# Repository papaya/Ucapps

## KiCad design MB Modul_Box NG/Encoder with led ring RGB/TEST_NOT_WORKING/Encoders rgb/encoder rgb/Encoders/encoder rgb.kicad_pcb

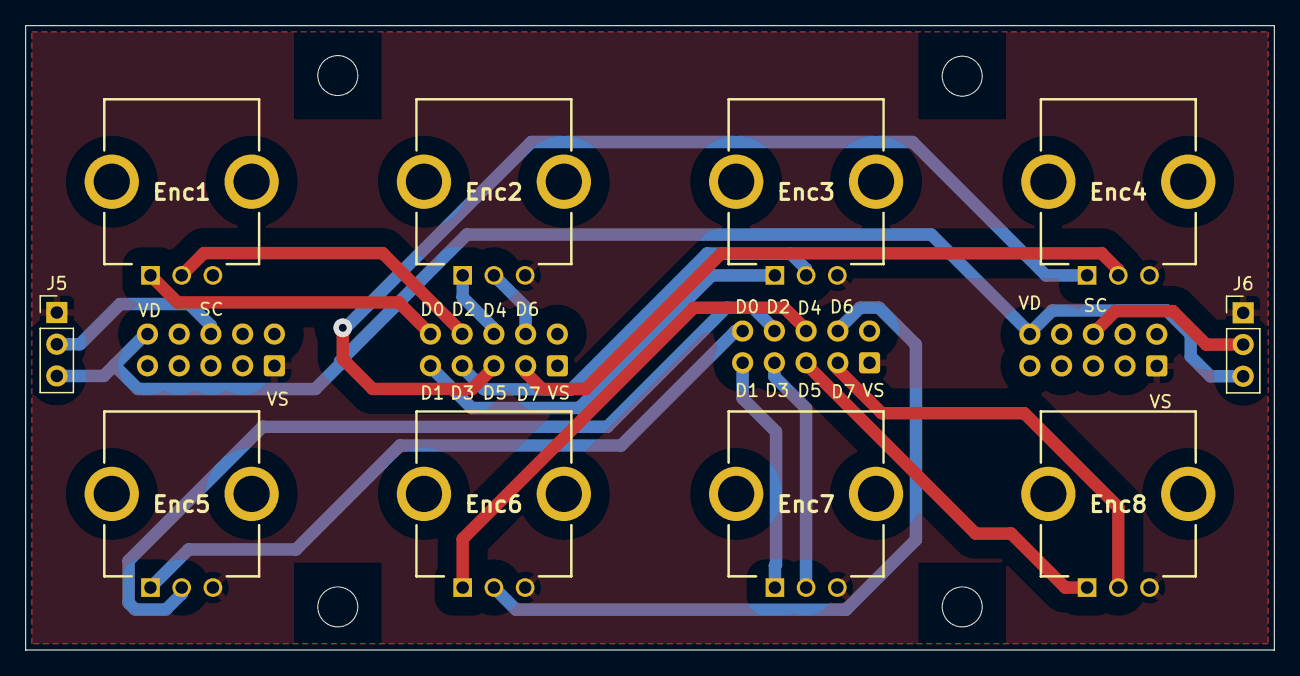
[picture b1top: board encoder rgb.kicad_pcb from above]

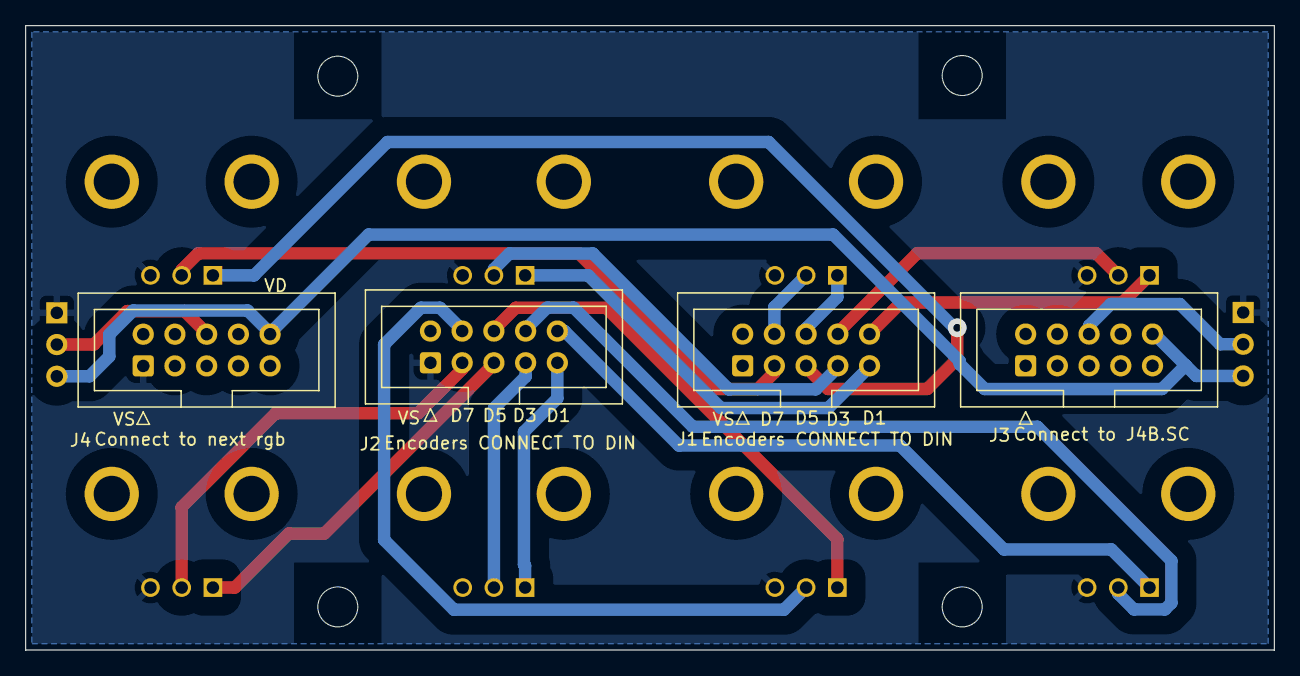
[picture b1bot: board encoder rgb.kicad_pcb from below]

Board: 2 copper layers, 100.0 x 50.0 mm, 18 parts (4 on the bottom side), 20 nets.

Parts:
Enc1, Enc2, Enc3, Enc4, Enc5, Enc6, Enc7, Enc8: RotaryEncoder; EC12E24204A8
H1, H2, H3, H4: MountingHole; MountingHole_3.2mm_M3
J1, J2, J3, J4: IDC-Header_2x05_P2.54mm_Vertical
J5, J6: Conn_01x03; PinHeader_1x03_P2.54mm_Vertical

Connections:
+5V: J3.10 (VD), J4.10 (VD), J5.3, J6.3
GND: Enc1.C, Enc2.C, Enc3.C, Enc4.C, Enc5.C, Enc6.C, Enc7.C, Enc8.C, J1.1 (vss), J2.1 (vss), J3.1 (vss), J4.1 (vss), J5.1, J6.1
unnamed: Enc1.A, J1.10 (D0)
unnamed: Enc3.A, J1.9 (D1)
unnamed: Enc1.B, J1.8 (D2)
unnamed: Enc3.B, J1.7 (D3)
unnamed: Enc2.A, J1.6 (D4)
unnamed: Enc4.A, J1.5 (D5)
unnamed: Enc2.B, J1.4 (D6)
unnamed: Enc4.B, J1.3 (D7)
unnamed: Enc5.A, J2.10 (D0)
unnamed: Enc7.A, J2.9 (D1)
unnamed: Enc5.B, J2.8 (D2)
unnamed: Enc7.B, J2.7 (D3)
unnamed: Enc6.A, J2.6 (D4)
unnamed: Enc8.A, J2.5 (D5)
unnamed: Enc6.B, J2.4 (D6)
unnamed: Enc8.B, J2.3 (D7)
unnamed: J3.6 (SC), J5.2
unnamed: J4.6 (SC), J6.2

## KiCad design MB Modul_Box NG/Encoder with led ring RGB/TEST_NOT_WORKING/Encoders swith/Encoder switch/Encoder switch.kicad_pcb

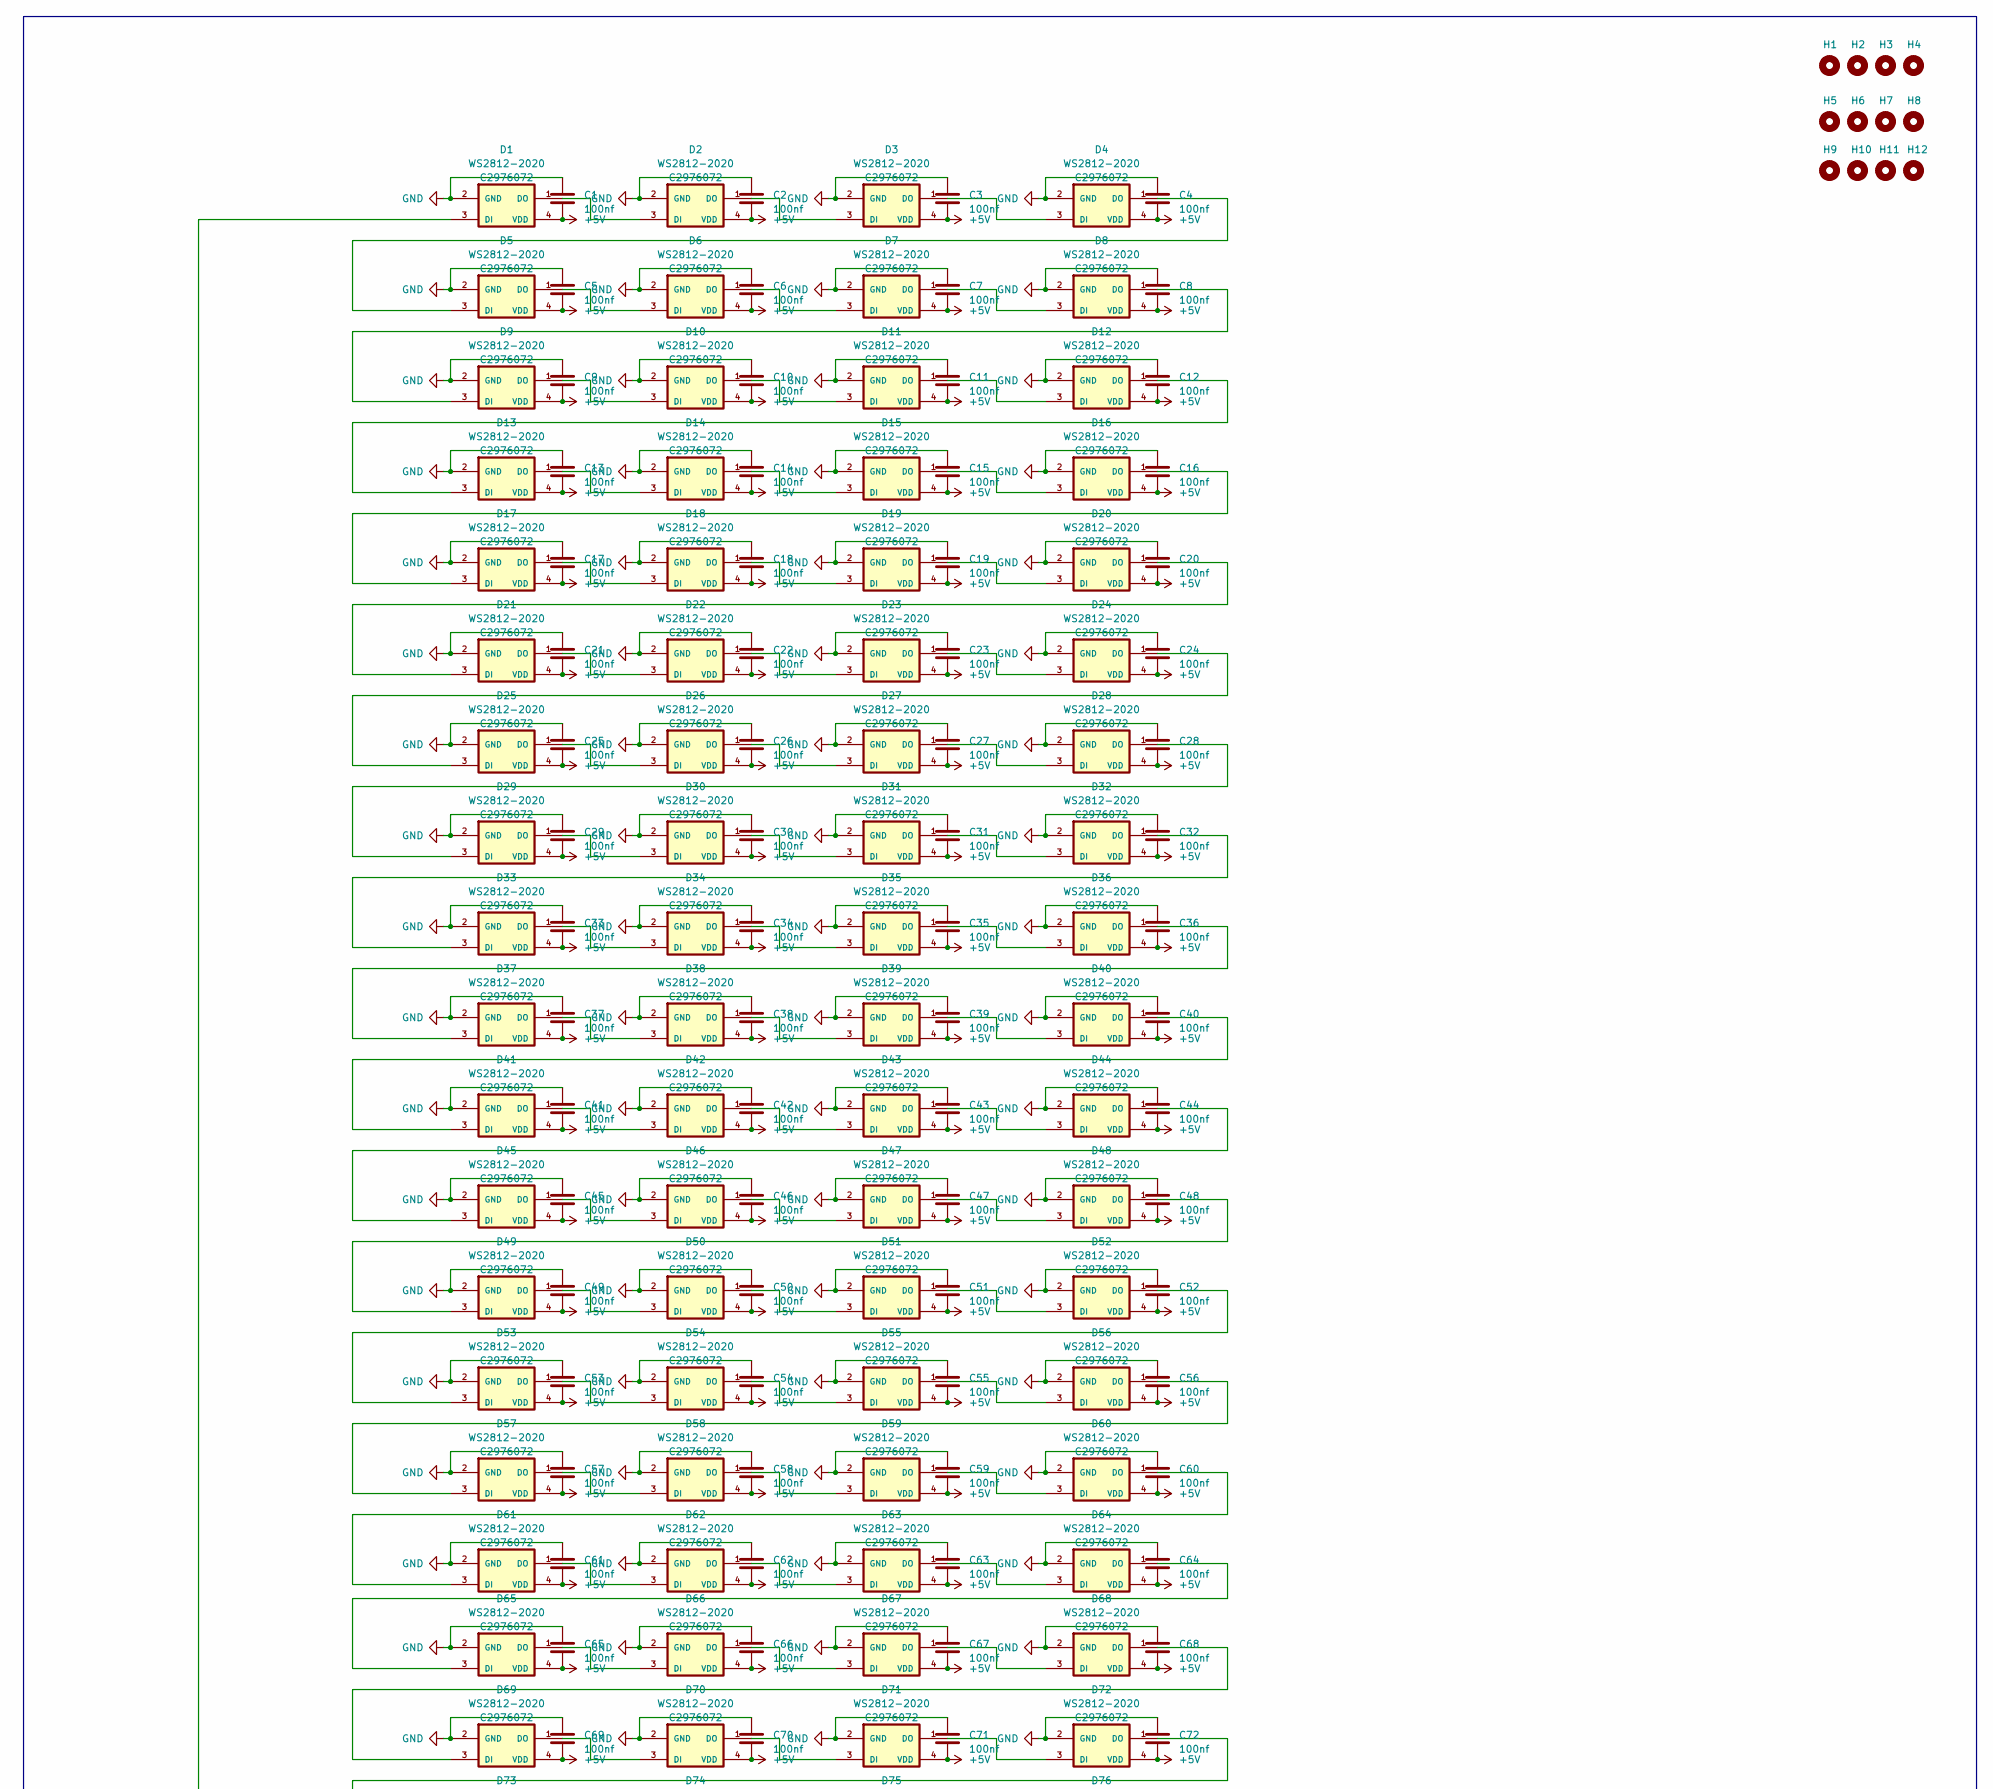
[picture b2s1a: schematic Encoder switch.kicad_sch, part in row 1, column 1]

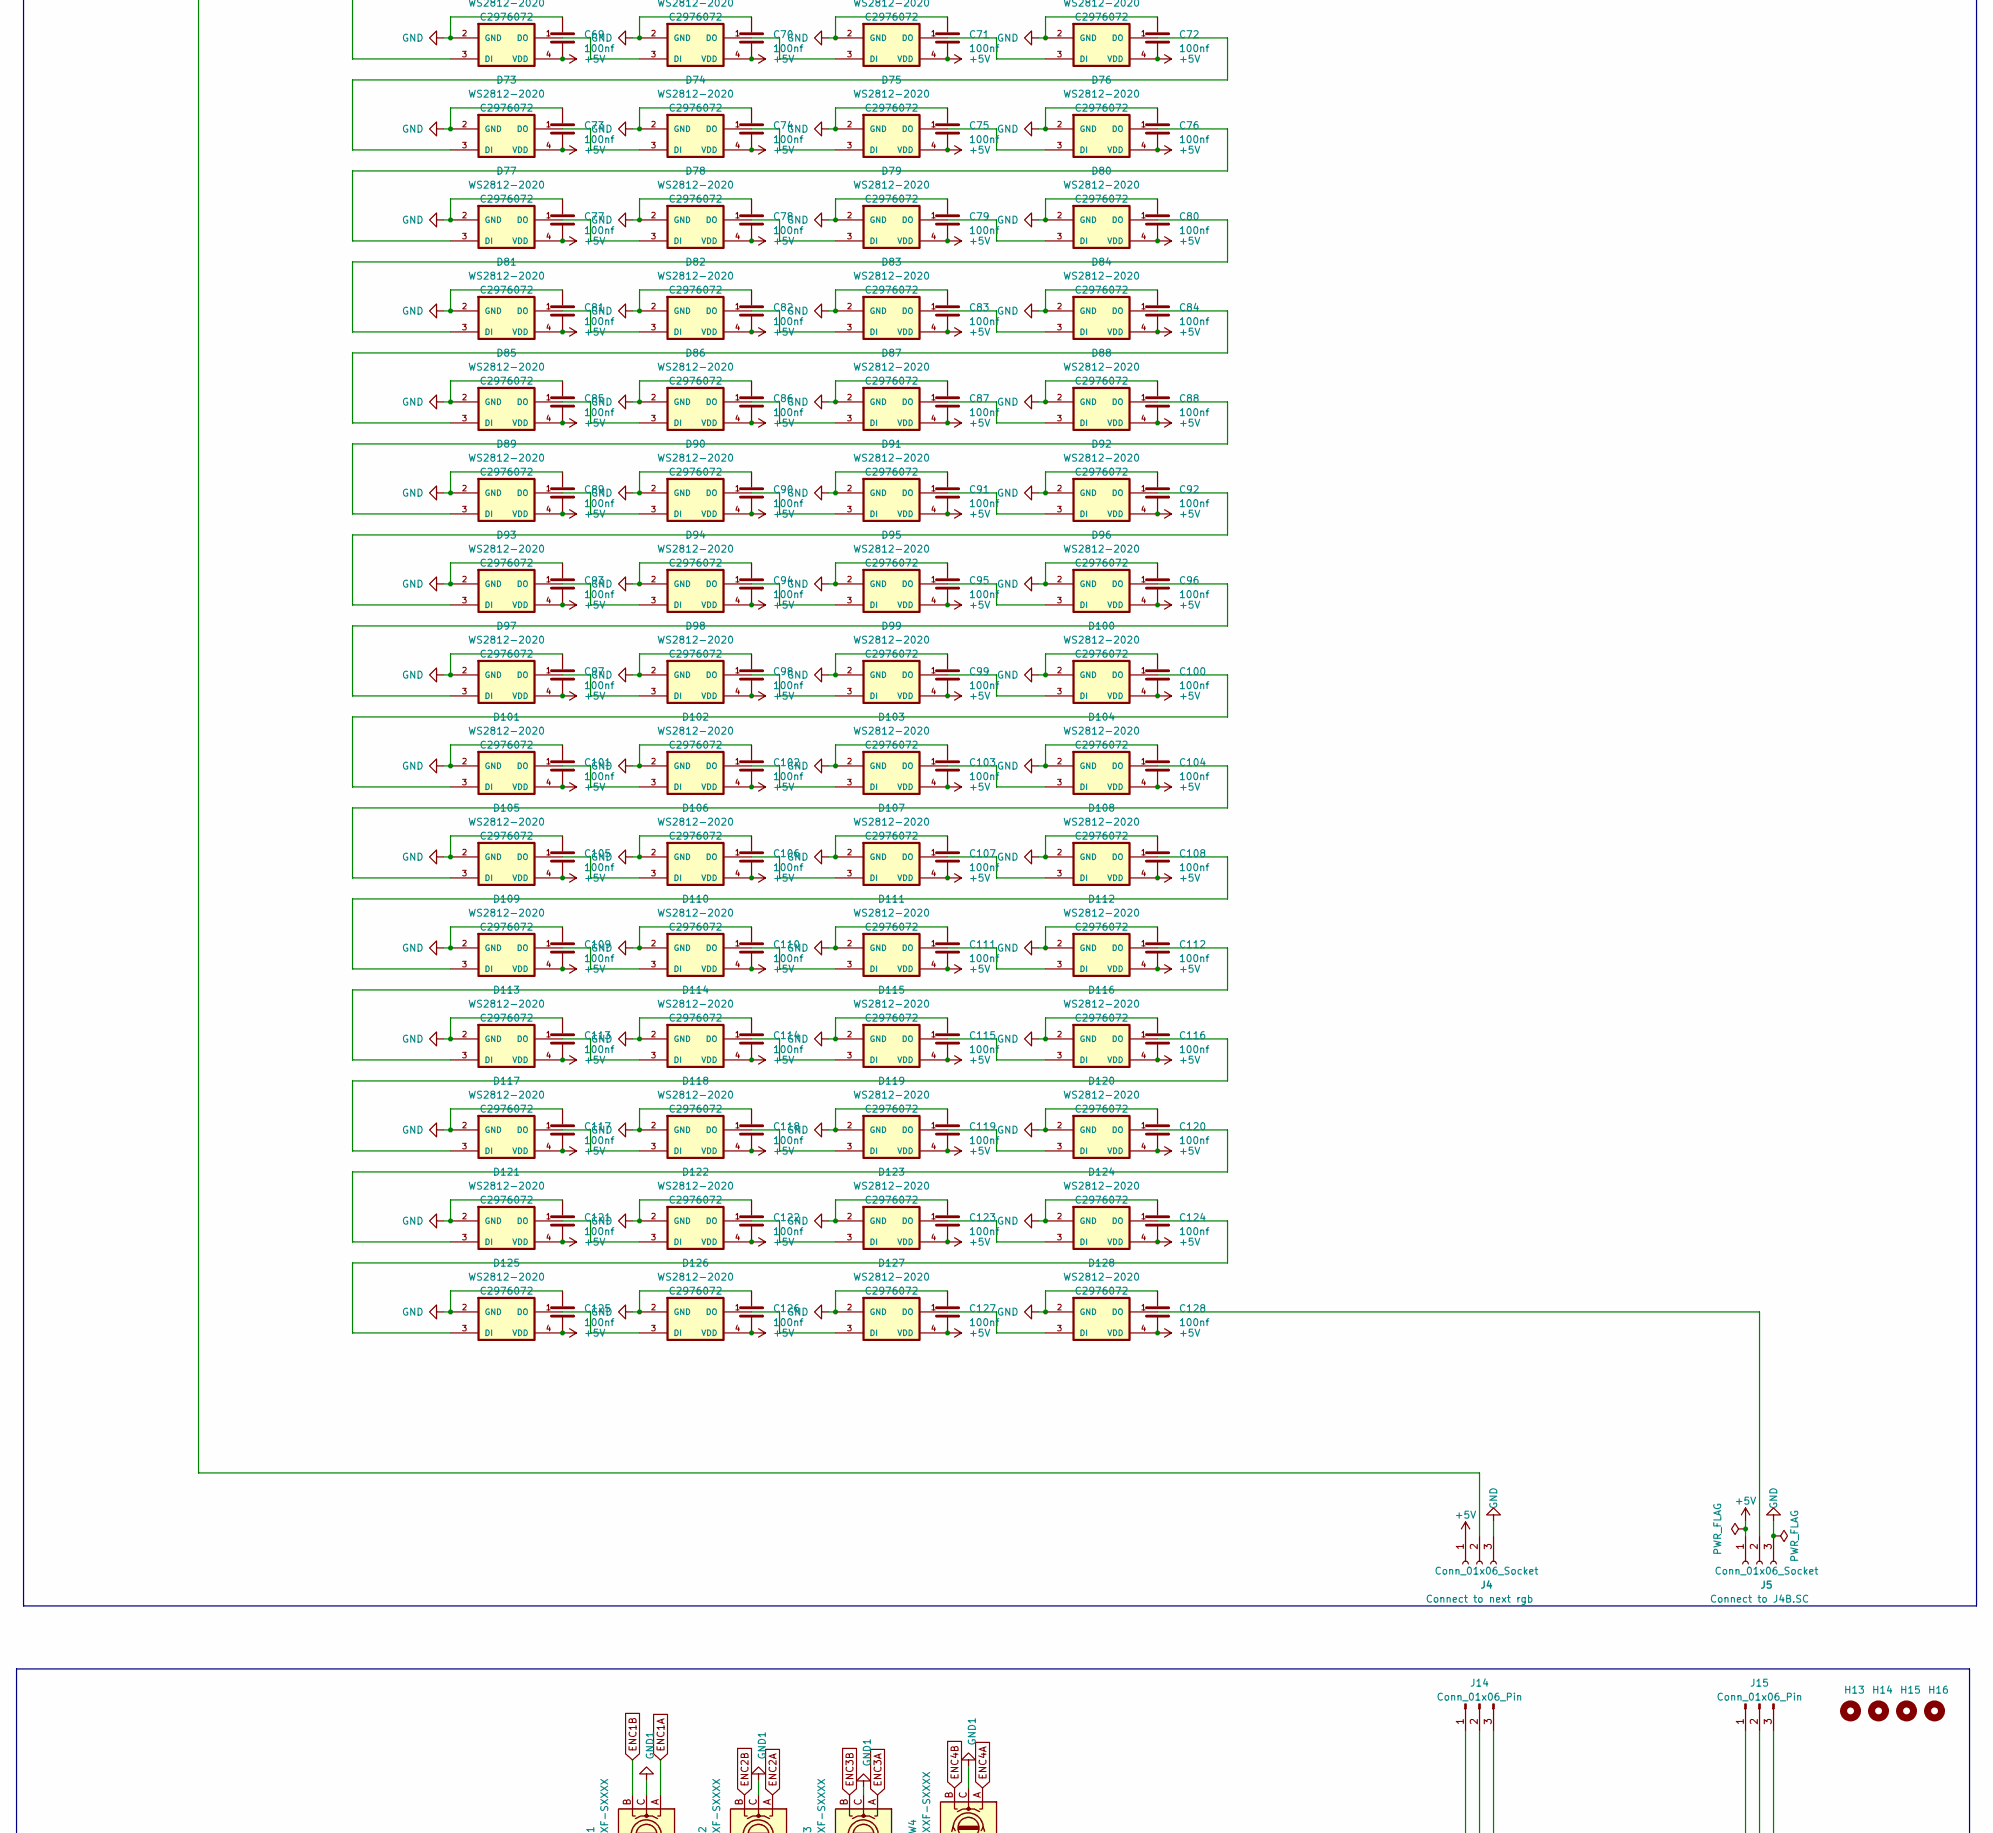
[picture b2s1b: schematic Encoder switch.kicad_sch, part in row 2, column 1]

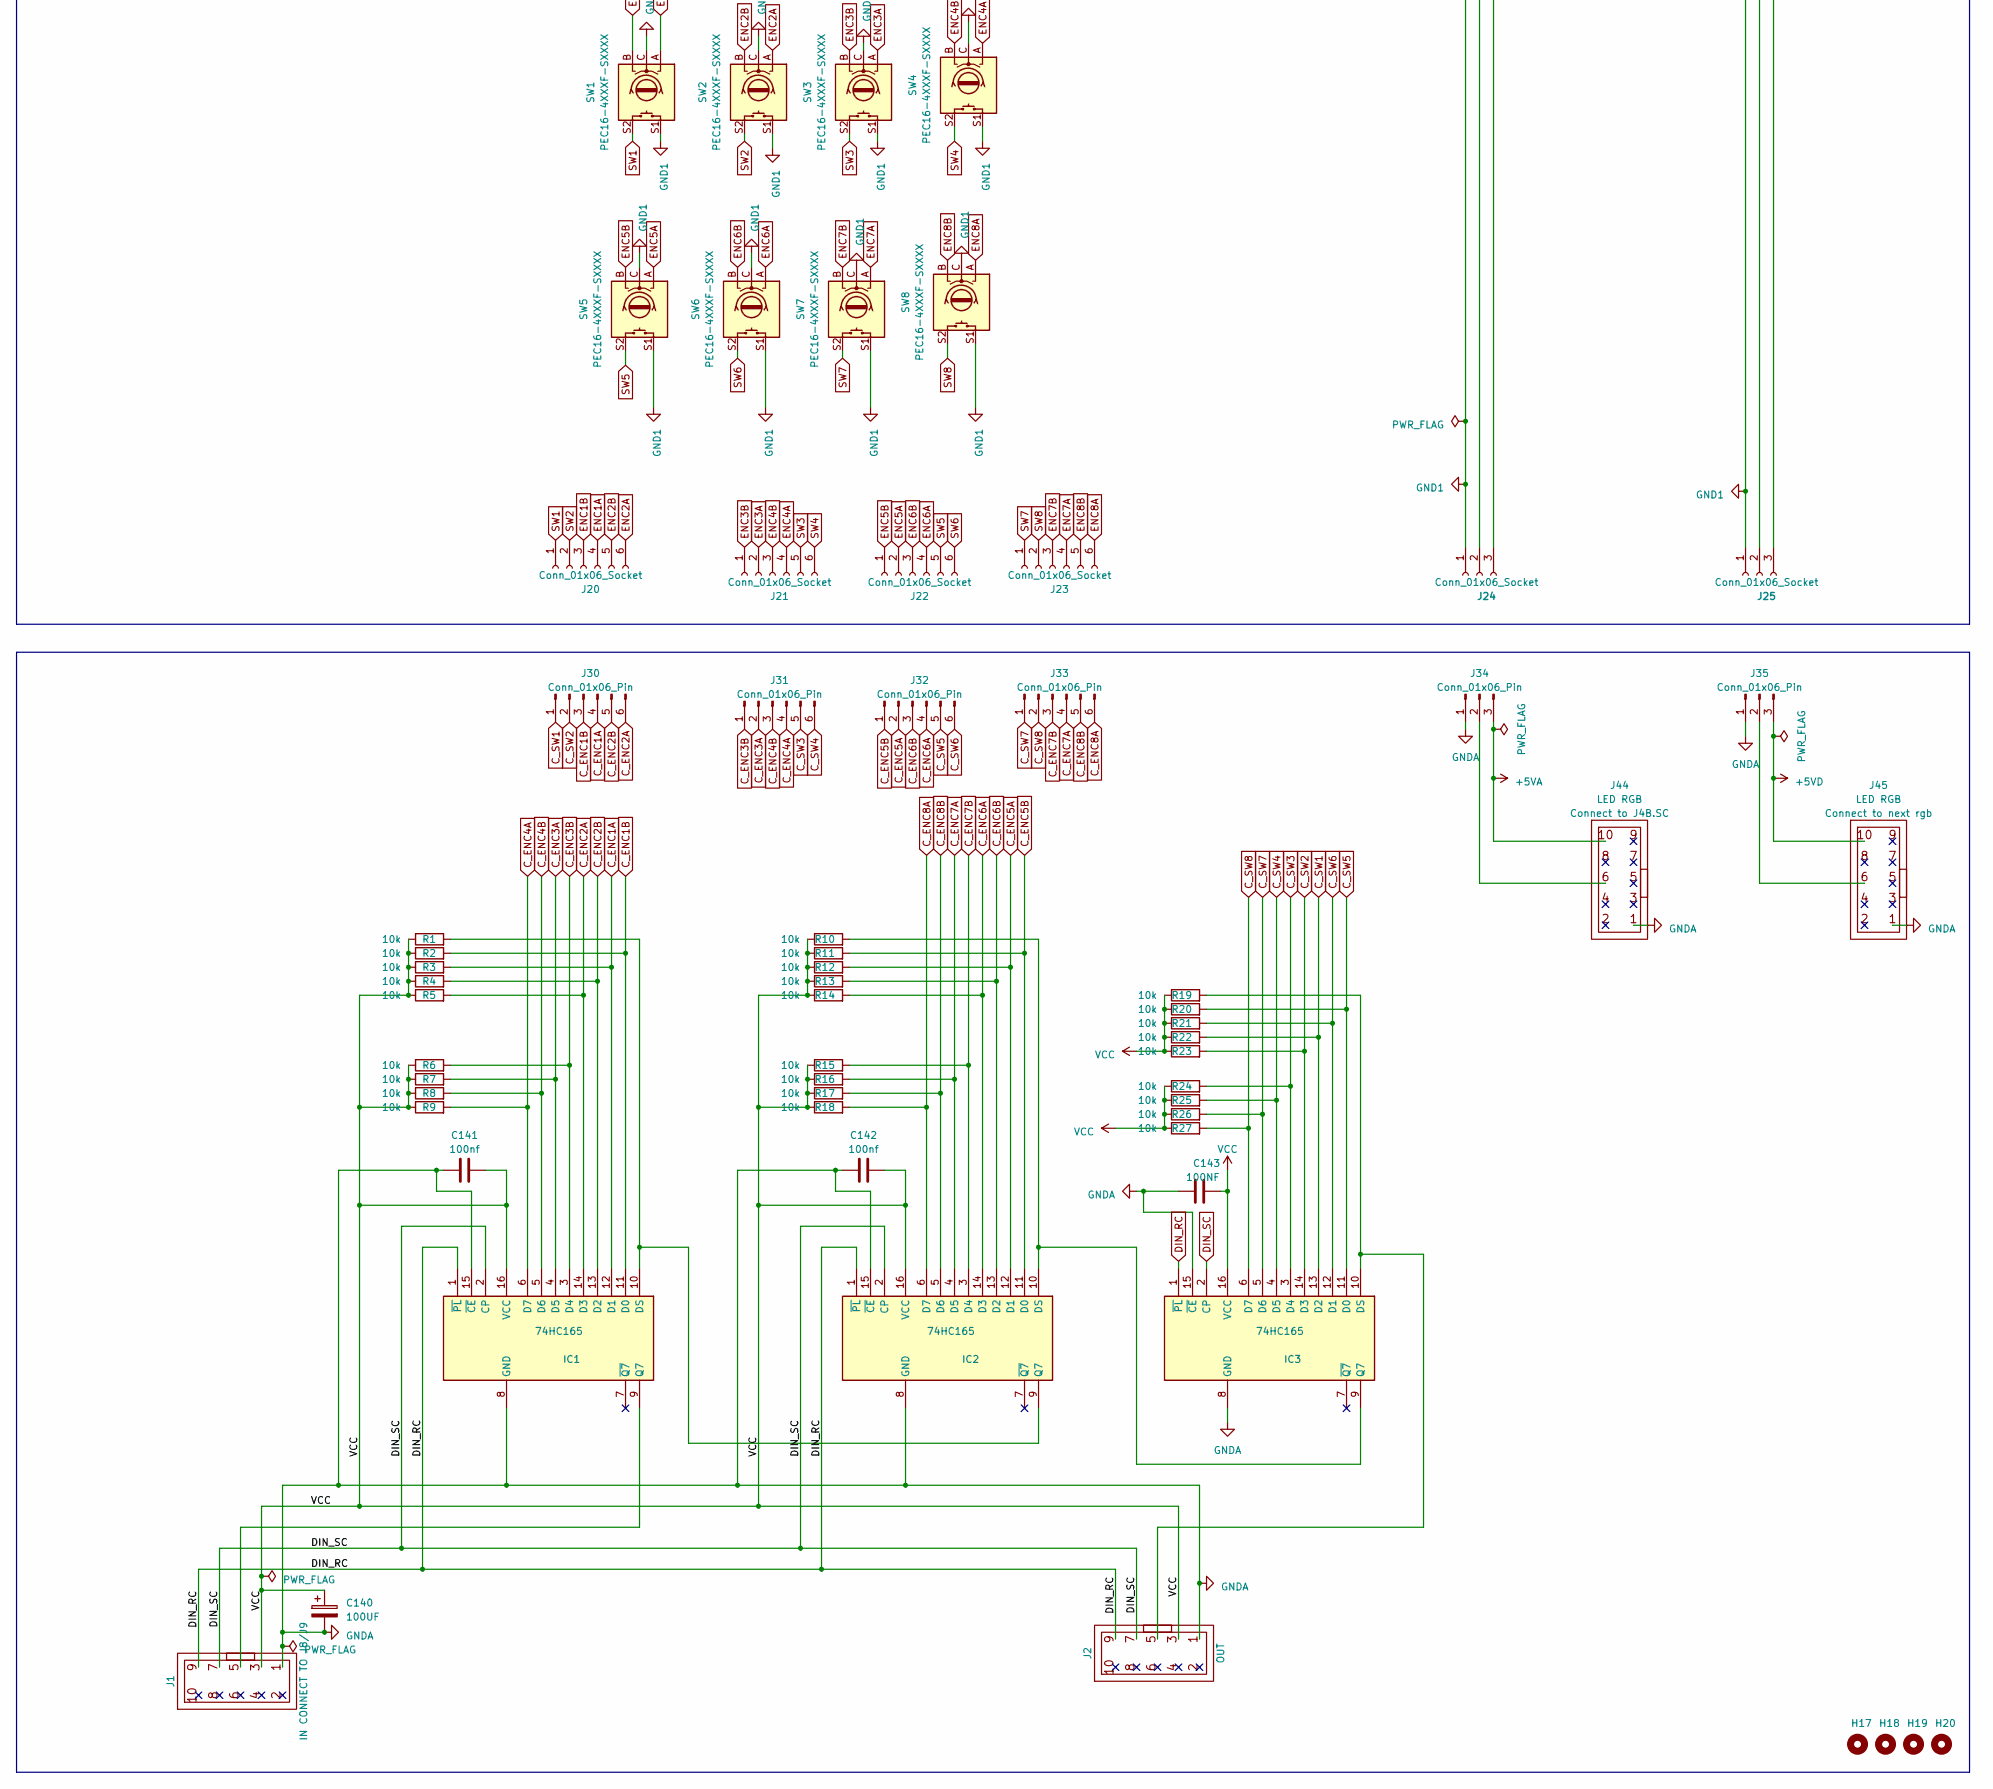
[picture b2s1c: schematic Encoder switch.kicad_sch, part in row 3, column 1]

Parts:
C1, C2, C3, C4, C5, C6, C7, C8, C9, C10, C11, C12, C13, C14, C15, C16, C17, C18, C19, C20, C21, C22, C23, C24, C25, C26, C27, C28, C29, C30, C31, C32, C33, C34, C35, C36, C37, C38, C39, C40, C41, C42, C43, C44, C45, C46, C47, C48, C49, C50, C51, C52, C53, C54, C55, C56, C57, C58, C59, C60, C61, C62, C63, C64, C65, C66, C67, C68, C69, C70, C71, C72, C73, C74, C75, C76, C77, C78, C79, C80, C81, C82, C83, C84, C85, C86, C87, C88, C89, C90, C91, C92, C93, C94, C95, C96, C97, C98, C99, C100, C101, C102, C103, C104, C105, C106, C107, C108, C109, C110, C111, C112, C113, C114, C115, C116, C117, C118, C119, C120, C121, C122, C123, C124, C125, C126, C127, C128: 100nf; CAPC1005X55N; JLCPCB Part # C1525
C140: 100UF; CP_Radial_D6.3mm_P2.50mm
C141, C142: 100nf; C_0603_1608Metric; JLCPCB Part # C14663
C143: 100NF; C_0603_1608Metric; JLCPCB Part # C14663
D1, D2, D3, D4, D5, D6, D7, D8, D9, D10, D11, D12, D13, D14, D15, D16, D17, D18, D19, D20, D21, D22, D23, D24, D25, D26, D27, D28, D29, D30, D31, D32, D33, D34, D35, D36, D37, D38, D39, D40, D41, D42, D43, D44, D45, D46, D47, D48, D49, D50, D51, D52, D53, D54, D55, D56, D57, D58, D59, D60, D61, D62, D63, D64, D65, D66, D67, D68, D69, D70, D71, D72, D73, D74, D75, D76, D77, D78, D79, D80, D81, D82, D83, D84, D85, D86, D87, D88, D89, D90, D91, D92, D93, D94, D95, D96, D97, D98, D99, D100, D101, D102, D103, D104, D105, D106, D107, D108, D109, D110, D111, D112, D113, D114, D115, D116, D117, D118, D119, D120, D121, D122, D123, D124, D125, D126, D127, D128: WS2812-2020; LED_WS2812B-2020_PLCC4_2.0x2.0mm; JLCPCB Part # C2976072
H1, H2, H3, H4, H13, H14, H15, H16, H17, H18, H19, H20: MountingHole; MountingHole_3.2mm_M3
H5, H6, H7, H8, H9, H10, H11, H12: MountingHole; Hole_9.5mm
IC1, IC2, IC3: 74HC165; SOIC-16_3.9x9.9mm_P1.27mm; JLCPCB Part # C5613
J1, J2: sin_in; IDC-Header_2x05_P2.54mm_Vertical
J4, J5, J24, J25: Conn_01x06_Socket; PinSocket_1x03_P2.54mm_Vertical
J14, J15, J34, J35: Conn_01x06_Pin; PinHeader_1x03_P2.54mm_Vertical
J20, J21, J22, J23: Conn_01x06_Socket; PinSocket_1x06_P2.54mm_Vertical
J30, J31, J32, J33: Conn_01x06_Pin; PinHeader_1x06_P2.54mm_Vertical
J44, J45: IDC-Header_2x05_P2.54mm_Vertical
R1, R2, R3, R4, R5, R6, R7, R8, R9, R10, R11, R12, R13, R14, R15, R16, R17, R18, R19, R20, R21, R22, R23, R24, R25, R26, R27: 10k; R_0603_1608Metric; JLCPCB Part # C1035
SW1, SW2, SW3, SW4, SW5, SW6, SW7, SW8: PEC16-4XXXF-SXXXX; PEC164120FS0012

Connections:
+5V: C1.2, C2.2, C3.2, C4.2, C5.2, C6.2, C7.2, C8.2, C9.2, C10.2, C11.2, C12.2, C13.2, C14.2, C15.2, C16.2, C17.2, C18.2, C19.2, C20.2, C21.2, C22.2, C23.2, C24.2, C25.2, C26.2, C27.2, C28.2, C29.2, C30.2, C31.2, C32.2, C33.2, C34.2, C35.2, C36.2, C37.2, C38.2, C39.2, C40.2, C41.2, C42.2, C43.2, C44.2, C45.2, C46.2, C47.2, C48.2, C49.2, C50.2, C51.2, C52.2, C53.2, C54.2, C55.2, C56.2, C57.2, C58.2, C59.2, C60.2, C61.2, C62.2, C63.2, C64.2, C65.2, C66.2, C67.2, C68.2, C69.2, C70.2, C71.2, C72.2, C73.2, C74.2, C75.2, C76.2, C77.2, C78.2, C79.2, C80.2, C81.2, C82.2, C83.2, C84.2, C85.2, C86.2, C87.2, C88.2, C89.2, C90.2, C91.2, C92.2, C93.2, C94.2, C95.2, C96.2, C97.2, C98.2, C99.2, C100.2, C101.2, C102.2, C103.2, C104.2, C105.2, C106.2, C107.2, C108.2, C109.2, C110.2, C111.2, C112.2, C113.2, C114.2, C115.2, C116.2, C117.2, C118.2, C119.2, C120.2, C121.2, C122.2, C123.2, C124.2, C125.2, C126.2, C127.2, C128.2, D1.4 (VDD), D2.4 (VDD), D3.4 (VDD), D4.4 (VDD), D5.4 (VDD), D6.4 (VDD), D7.4 (VDD), D8.4 (VDD), D9.4 (VDD), D10.4 (VDD), D11.4 (VDD), D12.4 (VDD), D13.4 (VDD), D14.4 (VDD), D15.4 (VDD), D16.4 (VDD), D17.4 (VDD), D18.4 (VDD), D19.4 (VDD), D20.4 (VDD), D21.4 (VDD), D22.4 (VDD), D23.4 (VDD), D24.4 (VDD), D25.4 (VDD), D26.4 (VDD), D27.4 (VDD), D28.4 (VDD), D29.4 (VDD), D30.4 (VDD), D31.4 (VDD), D32.4 (VDD), D33.4 (VDD), D34.4 (VDD), D35.4 (VDD), D36.4 (VDD), D37.4 (VDD), D38.4 (VDD), D39.4 (VDD), D40.4 (VDD), D41.4 (VDD), D42.4 (VDD), D43.4 (VDD), D44.4 (VDD), D45.4 (VDD), D46.4 (VDD), D47.4 (VDD), D48.4 (VDD), D49.4 (VDD), D50.4 (VDD), D51.4 (VDD), D52.4 (VDD), D53.4 (VDD), D54.4 (VDD), D55.4 (VDD), D56.4 (VDD), D57.4 (VDD), D58.4 (VDD), D59.4 (VDD), D60.4 (VDD), D61.4 (VDD), D62.4 (VDD), D63.4 (VDD), D64.4 (VDD), D65.4 (VDD), D66.4 (VDD), D67.4 (VDD), D68.4 (VDD), D69.4 (VDD), D70.4 (VDD), D71.4 (VDD), D72.4 (VDD), D73.4 (VDD), D74.4 (VDD), D75.4 (VDD), D76.4 (VDD), D77.4 (VDD), D78.4 (VDD), D79.4 (VDD), D80.4 (VDD), D81.4 (VDD), D82.4 (VDD), D83.4 (VDD), D84.4 (VDD), D85.4 (VDD), D86.4 (VDD), D87.4 (VDD), D88.4 (VDD), D89.4 (VDD), D90.4 (VDD), D91.4 (VDD), D92.4 (VDD), D93.4 (VDD), D94.4 (VDD), D95.4 (VDD), D96.4 (VDD), D97.4 (VDD), D98.4 (VDD), D99.4 (VDD), D100.4 (VDD), D101.4 (VDD), D102.4 (VDD), D103.4 (VDD), D104.4 (VDD), D105.4 (VDD), D106.4 (VDD), D107.4 (VDD), D108.4 (VDD), D109.4 (VDD), D110.4 (VDD), D111.4 (VDD), D112.4 (VDD), D113.4 (VDD), D114.4 (VDD), D115.4 (VDD), D116.4 (VDD), D117.4 (VDD), D118.4 (VDD), D119.4 (VDD), D120.4 (VDD), D121.4 (VDD), D122.4 (VDD), D123.4 (VDD), D124.4 (VDD), D125.4 (VDD), D126.4 (VDD), D127.4 (VDD), D128.4 (VDD), J4.1, J5.1
+5VA: J34.3, J44.10
+5VD: J35.3, J45.10
C_ENC1A: IC1.12 (D1), J30.4, R3.2
C_ENC1B: IC1.11 (D0), J30.3, R2.2
C_ENC2A: IC1.14 (D3), J30.6, R5.2
C_ENC2B: IC1.13 (D2), J30.5, R4.2
C_ENC3A: IC1.4 (D5), J31.2, R7.2
C_ENC3B: IC1.3 (D4), J31.1, R6.2
C_ENC4A: IC1.6 (D7), J31.4, R9.2
C_ENC4B: IC1.5 (D6), J31.3, R8.2
C_ENC5A: IC2.12 (D1), J32.2, R12.2
C_ENC5B: IC2.11 (D0), J32.1, R11.2
C_ENC6A: IC2.14 (D3), J32.4, R14.2
C_ENC6B: IC2.13 (D2), J32.3, R13.2
C_ENC7A: IC2.4 (D5), J33.4, R16.2
C_ENC7B: IC2.3 (D4), J33.3, R15.2
C_ENC8A: IC2.6 (D7), J33.6, R18.2
C_ENC8B: IC2.5 (D6), J33.5, R17.2
C_SW1: IC3.13 (D2), J30.1, R22.2
C_SW2: IC3.14 (D3), J30.2, R23.2
C_SW3: IC3.3 (D4), J31.5, R24.2
C_SW4: IC3.4 (D5), J31.6, R25.2
C_SW5: IC3.11 (D0), J32.5, R20.2
C_SW6: IC3.12 (D1), J32.6, R21.2
C_SW7: IC3.5 (D6), J33.1, R26.2
C_SW8: IC3.6 (D7), J33.2, R27.2
DIN_RC: IC1.1 (~PL), IC2.1 (~PL), IC3.1 (~PL), J1.9, J2.9
DIN_SC: IC1.2 (CP), IC2.2 (CP), IC3.2 (CP), J1.7, J2.7
ENC1A: J20.4, SW1.A
ENC1B: J20.3, SW1.B
ENC2A: J20.6, SW2.A
ENC2B: J20.5, SW2.B
ENC3A: J21.2, SW3.A
ENC3B: J21.1, SW3.B
ENC4A: J21.4, SW4.A
ENC4B: J21.3, SW4.B
ENC5A: J22.2, SW5.A
ENC5B: J22.1, SW5.B
ENC6A: J22.4, SW6.A
ENC6B: J22.3, SW6.B
ENC7A: J23.4, SW7.A
ENC7B: J23.3, SW7.B
ENC8A: J23.6, SW8.A
ENC8B: J23.5, SW8.B
GND: C1.1, C2.1, C3.1, C4.1, C5.1, C6.1, C7.1, C8.1, C9.1, C10.1, C11.1, C12.1, C13.1, C14.1, C15.1, C16.1, C17.1, C18.1, C19.1, C20.1, C21.1, C22.1, C23.1, C24.1, C25.1, C26.1, C27.1, C28.1, C29.1, C30.1, C31.1, C32.1, C33.1, C34.1, C35.1, C36.1, C37.1, C38.1, C39.1, C40.1, C41.1, C42.1, C43.1, C44.1, C45.1, C46.1, C47.1, C48.1, C49.1, C50.1, C51.1, C52.1, C53.1, C54.1, C55.1, C56.1, C57.1, C58.1, C59.1, C60.1, C61.1, C62.1, C63.1, C64.1, C65.1, C66.1, C67.1, C68.1, C69.1, C70.1, C71.1, C72.1, C73.1, C74.1, C75.1, C76.1, C77.1, C78.1, C79.1, C80.1, C81.1, C82.1, C83.1, C84.1, C85.1, C86.1, C87.1, C88.1, C89.1, C90.1, C91.1, C92.1, C93.1, C94.1, C95.1, C96.1, C97.1, C98.1, C99.1, C100.1, C101.1, C102.1, C103.1, C104.1, C105.1, C106.1, C107.1, C108.1, C109.1, C110.1, C111.1, C112.1, C113.1, C114.1, C115.1, C116.1, C117.1, C118.1, C119.1, C120.1, C121.1, C122.1, C123.1, C124.1, C125.1, C126.1, C127.1, C128.1, D1.2 (GND), D2.2 (GND), D3.2 (GND), D4.2 (GND), D5.2 (GND), D6.2 (GND), D7.2 (GND), D8.2 (GND), D9.2 (GND), D10.2 (GND), D11.2 (GND), D12.2 (GND), D13.2 (GND), D14.2 (GND), D15.2 (GND), D16.2 (GND), D17.2 (GND), D18.2 (GND), D19.2 (GND), D20.2 (GND), D21.2 (GND), D22.2 (GND), D23.2 (GND), D24.2 (GND), D25.2 (GND), D26.2 (GND), D27.2 (GND), D28.2 (GND), D29.2 (GND), D30.2 (GND), D31.2 (GND), D32.2 (GND), D33.2 (GND), D34.2 (GND), D35.2 (GND), D36.2 (GND), D37.2 (GND), D38.2 (GND), D39.2 (GND), D40.2 (GND), D41.2 (GND), D42.2 (GND), D43.2 (GND), D44.2 (GND), D45.2 (GND), D46.2 (GND), D47.2 (GND), D48.2 (GND), D49.2 (GND), D50.2 (GND), D51.2 (GND), D52.2 (GND), D53.2 (GND), D54.2 (GND), D55.2 (GND), D56.2 (GND), D57.2 (GND), D58.2 (GND), D59.2 (GND), D60.2 (GND), D61.2 (GND), D62.2 (GND), D63.2 (GND), D64.2 (GND), D65.2 (GND), D66.2 (GND), D67.2 (GND), D68.2 (GND), D69.2 (GND), D70.2 (GND), D71.2 (GND), D72.2 (GND), D73.2 (GND), D74.2 (GND), D75.2 (GND), D76.2 (GND), D77.2 (GND), D78.2 (GND), D79.2 (GND), D80.2 (GND), D81.2 (GND), D82.2 (GND), D83.2 (GND), D84.2 (GND), D85.2 (GND), D86.2 (GND), D87.2 (GND), D88.2 (GND), D89.2 (GND), D90.2 (GND), D91.2 (GND), D92.2 (GND), D93.2 (GND), D94.2 (GND), D95.2 (GND), D96.2 (GND), D97.2 (GND), D98.2 (GND), D99.2 (GND), D100.2 (GND), D101.2 (GND), D102.2 (GND), D103.2 (GND), D104.2 (GND), D105.2 (GND), D106.2 (GND), D107.2 (GND), D108.2 (GND), D109.2 (GND), D110.2 (GND), D111.2 (GND), D112.2 (GND), D113.2 (GND), D114.2 (GND), D115.2 (GND), D116.2 (GND), D117.2 (GND), D118.2 (GND), D119.2 (GND), D120.2 (GND), D121.2 (GND), D122.2 (GND), D123.2 (GND), D124.2 (GND), D125.2 (GND), D126.2 (GND), D127.2 (GND), D128.2 (GND), J4.3, J5.3
GND1: J14.1, J15.1, J24.1, J25.1, SW1.C, SW1.S1, SW2.C, SW2.S1, SW3.C, SW3.S1, SW4.C, SW4.S1, SW5.C, SW5.S1, SW6.C, SW6.S1, SW7.C, SW7.S1, SW8.C, SW8.S1
GNDA: C140.2, C141.2, C142.2, C143.1, IC1.8 (GND), IC1.15 (~CE), IC2.8 (GND), IC2.15 (~CE), IC3.8 (GND), IC3.15 (~CE), J1.1, J2.1, J34.1, J35.1, J44.1, J45.1
unnamed: D1.3 (DI), J4.2
unnamed: D1.1 (DO), D2.3 (DI)
unnamed: D2.1 (DO), D3.3 (DI)
unnamed: D3.1 (DO), D4.3 (DI)
unnamed: D4.1 (DO), D5.3 (DI)
unnamed: D5.1 (DO), D6.3 (DI)
unnamed: D6.1 (DO), D7.3 (DI)
unnamed: D7.1 (DO), D8.3 (DI)
unnamed: D8.1 (DO), D9.3 (DI)
unnamed: D9.1 (DO), D10.3 (DI)
unnamed: D10.1 (DO), D11.3 (DI)
unnamed: D11.1 (DO), D12.3 (DI)
unnamed: D12.1 (DO), D13.3 (DI)
unnamed: D13.1 (DO), D14.3 (DI)
unnamed: D14.1 (DO), D15.3 (DI)
unnamed: D15.1 (DO), D16.3 (DI)
unnamed: D16.1 (DO), D17.3 (DI)
unnamed: D17.1 (DO), D18.3 (DI)
unnamed: D18.1 (DO), D19.3 (DI)
unnamed: D19.1 (DO), D20.3 (DI)
unnamed: D20.1 (DO), D21.3 (DI)
unnamed: D21.1 (DO), D22.3 (DI)
unnamed: D22.1 (DO), D23.3 (DI)
unnamed: D23.1 (DO), D24.3 (DI)
unnamed: D24.1 (DO), D25.3 (DI)
unnamed: D25.1 (DO), D26.3 (DI)
unnamed: D26.1 (DO), D27.3 (DI)
unnamed: D27.1 (DO), D28.3 (DI)
unnamed: D28.1 (DO), D29.3 (DI)
unnamed: D29.1 (DO), D30.3 (DI)
unnamed: D30.1 (DO), D31.3 (DI)
unnamed: D31.1 (DO), D32.3 (DI)
unnamed: D32.1 (DO), D33.3 (DI)
unnamed: D33.1 (DO), D34.3 (DI)
unnamed: D34.1 (DO), D35.3 (DI)
unnamed: D35.1 (DO), D36.3 (DI)
unnamed: D36.1 (DO), D37.3 (DI)
unnamed: D37.1 (DO), D38.3 (DI)
unnamed: D38.1 (DO), D39.3 (DI)
unnamed: D39.1 (DO), D40.3 (DI)
unnamed: D40.1 (DO), D41.3 (DI)
unnamed: D41.1 (DO), D42.3 (DI)
unnamed: D42.1 (DO), D43.3 (DI)
unnamed: D43.1 (DO), D44.3 (DI)
unnamed: D44.1 (DO), D45.3 (DI)
unnamed: D45.1 (DO), D46.3 (DI)
unnamed: D46.1 (DO), D47.3 (DI)
unnamed: D47.1 (DO), D48.3 (DI)
unnamed: D48.1 (DO), D49.3 (DI)
unnamed: D49.1 (DO), D50.3 (DI)
unnamed: D50.1 (DO), D51.3 (DI)
unnamed: D51.1 (DO), D52.3 (DI)
unnamed: D52.1 (DO), D53.3 (DI)
unnamed: D53.1 (DO), D54.3 (DI)
unnamed: D54.1 (DO), D55.3 (DI)
unnamed: D55.1 (DO), D56.3 (DI)
unnamed: D56.1 (DO), D57.3 (DI)
unnamed: D57.1 (DO), D58.3 (DI)
unnamed: D58.1 (DO), D59.3 (DI)
unnamed: D59.1 (DO), D60.3 (DI)
unnamed: D60.1 (DO), D61.3 (DI)
unnamed: D61.1 (DO), D62.3 (DI)
unnamed: D62.1 (DO), D63.3 (DI)
unnamed: D63.1 (DO), D64.3 (DI)
unnamed: D64.1 (DO), D65.3 (DI)
unnamed: D65.1 (DO), D66.3 (DI)
unnamed: D66.1 (DO), D67.3 (DI)
unnamed: D67.1 (DO), D68.3 (DI)
unnamed: D68.1 (DO), D69.3 (DI)
unnamed: D69.1 (DO), D70.3 (DI)
unnamed: D70.1 (DO), D71.3 (DI)
unnamed: D71.1 (DO), D72.3 (DI)
unnamed: D72.1 (DO), D73.3 (DI)
unnamed: D73.1 (DO), D74.3 (DI)
unnamed: D74.1 (DO), D75.3 (DI)
unnamed: D75.1 (DO), D76.3 (DI)
unnamed: D76.1 (DO), D77.3 (DI)
unnamed: D77.1 (DO), D78.3 (DI)
unnamed: D78.1 (DO), D79.3 (DI)
unnamed: D79.1 (DO), D80.3 (DI)
unnamed: D80.1 (DO), D81.3 (DI)
unnamed: D81.1 (DO), D82.3 (DI)
unnamed: D82.1 (DO), D83.3 (DI)
unnamed: D83.1 (DO), D84.3 (DI)
unnamed: D84.1 (DO), D85.3 (DI)
unnamed: D85.1 (DO), D86.3 (DI)
unnamed: D86.1 (DO), D87.3 (DI)
unnamed: D87.1 (DO), D88.3 (DI)
unnamed: D88.1 (DO), D89.3 (DI)
unnamed: D89.1 (DO), D90.3 (DI)
unnamed: D90.1 (DO), D91.3 (DI)
unnamed: D91.1 (DO), D92.3 (DI)
unnamed: D92.1 (DO), D93.3 (DI)
unnamed: D93.1 (DO), D94.3 (DI)
unnamed: D94.1 (DO), D95.3 (DI)
unnamed: D95.1 (DO), D96.3 (DI)
unnamed: D96.1 (DO), D97.3 (DI)
unnamed: D97.1 (DO), D98.3 (DI)
unnamed: D98.1 (DO), D99.3 (DI)
unnamed: D99.1 (DO), D100.3 (DI)
unnamed: D100.1 (DO), D101.3 (DI)
unnamed: D101.1 (DO), D102.3 (DI)
unnamed: D102.1 (DO), D103.3 (DI)
unnamed: D103.1 (DO), D104.3 (DI)
unnamed: D104.1 (DO), D105.3 (DI)
unnamed: D105.1 (DO), D106.3 (DI)
unnamed: D106.1 (DO), D107.3 (DI)
unnamed: D107.1 (DO), D108.3 (DI)
unnamed: D108.1 (DO), D109.3 (DI)
unnamed: D109.1 (DO), D110.3 (DI)
unnamed: D110.1 (DO), D111.3 (DI)
unnamed: D111.1 (DO), D112.3 (DI)
unnamed: D112.1 (DO), D113.3 (DI)
unnamed: D113.1 (DO), D114.3 (DI)
unnamed: D114.1 (DO), D115.3 (DI)
unnamed: D115.1 (DO), D116.3 (DI)
unnamed: D116.1 (DO), D117.3 (DI)
unnamed: D117.1 (DO), D118.3 (DI)
unnamed: D118.1 (DO), D119.3 (DI)
unnamed: D119.1 (DO), D120.3 (DI)
unnamed: D120.1 (DO), D121.3 (DI)
unnamed: D121.1 (DO), D122.3 (DI)
unnamed: D122.1 (DO), D123.3 (DI)
unnamed: D123.1 (DO), D124.3 (DI)
unnamed: D124.1 (DO), D125.3 (DI)
unnamed: D125.1 (DO), D126.3 (DI)
unnamed: D126.1 (DO), D127.3 (DI)
unnamed: D127.1 (DO), D128.3 (DI)
unnamed: D128.1 (DO), J5.2
unnamed: IC1.10 (DS), IC2.9 (Q7), R1.2
unnamed: IC1.9 (Q7), J1.5
unnamed: IC2.10 (DS), IC3.9 (Q7), R10.2
unnamed: IC3.10 (DS), J2.5, R19.2
unnamed: J14.2, J24.2
unnamed: J14.3, J24.3
unnamed: J15.2, J25.2
unnamed: J15.3, J25.3
unnamed: J34.2, J44.6
unnamed: J35.2, J45.6
SW1: J20.1, SW1.S2
SW2: J20.2, SW2.S2
SW3: J21.5, SW3.S2
SW4: J21.6, SW4.S2
SW5: J22.5, SW5.S2
SW6: J22.6, SW6.S2
SW7: J23.1, SW7.S2
SW8: J23.2, SW8.S2
VCC: C140.1, C141.1, C142.1, C143.2, IC1.16 (VCC), IC2.16 (VCC), IC3.16 (VCC), J1.3, J2.3, R1.1, R2.1, R3.1, R4.1, R5.1, R6.1, R7.1, R8.1, R9.1, R10.1, R11.1, R12.1, R13.1, R14.1, R15.1, R16.1, R17.1, R18.1, R19.1, R20.1, R21.1, R22.1, R23.1, R24.1, R25.1, R26.1, R27.1

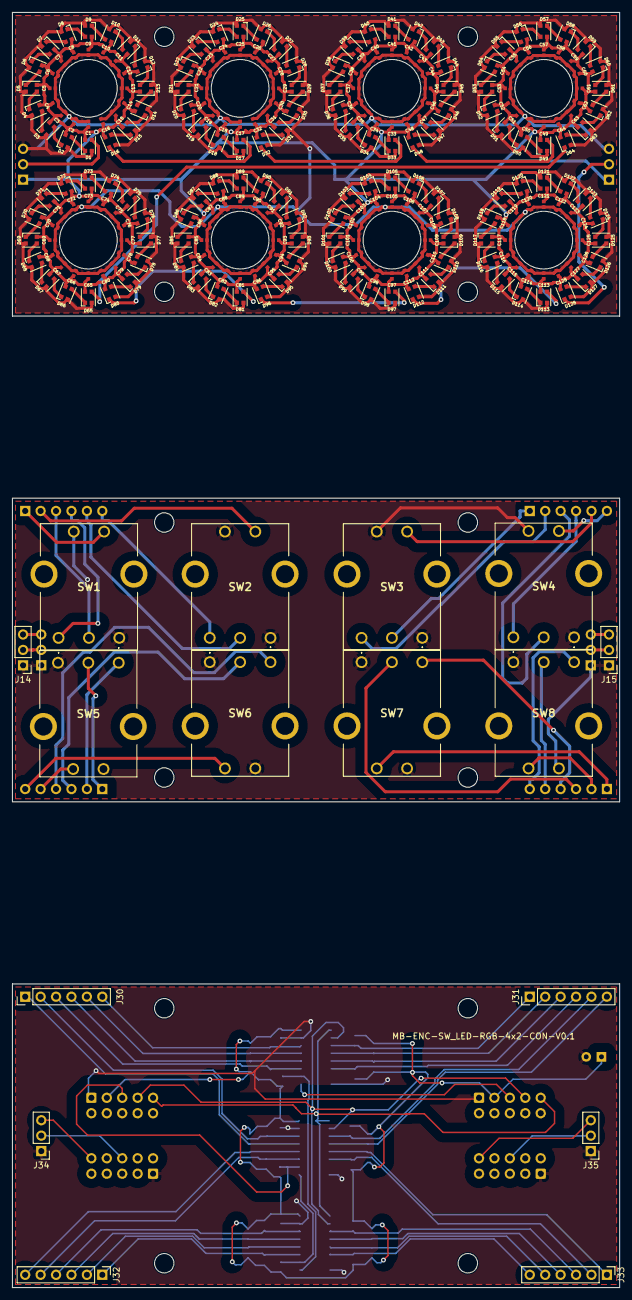
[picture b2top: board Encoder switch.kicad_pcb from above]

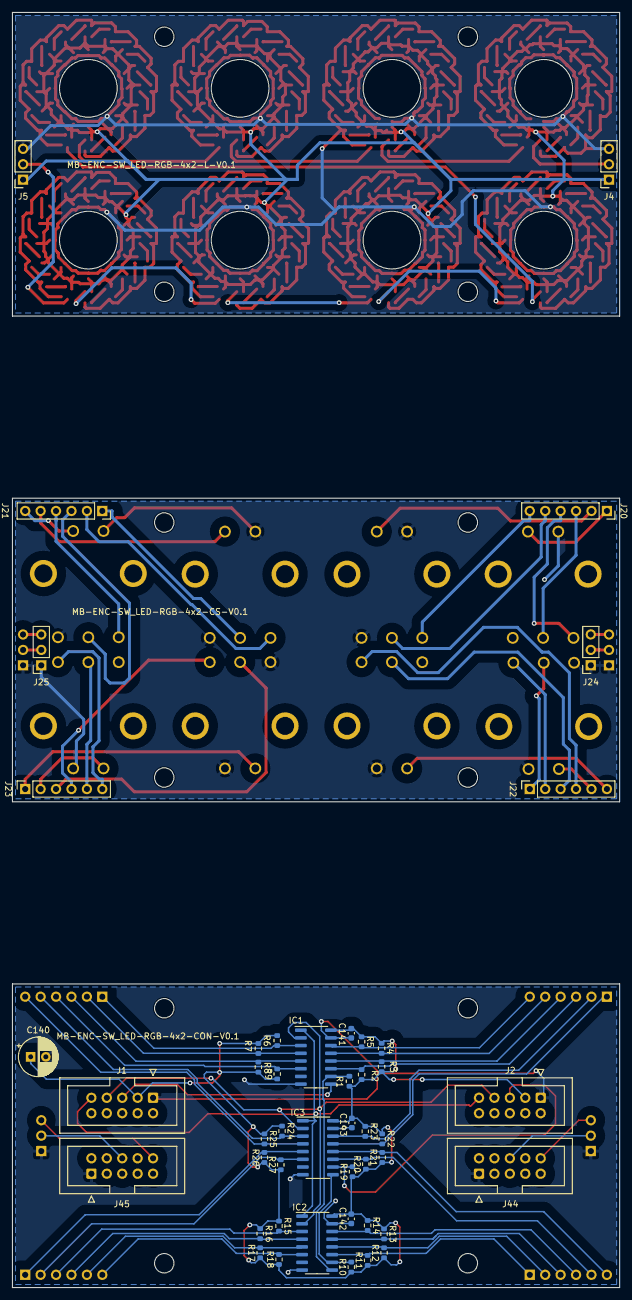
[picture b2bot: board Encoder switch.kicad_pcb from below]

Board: 2 copper layers, 100.0 x 50.0 mm, 338 parts (46 on the bottom side), 196 nets.

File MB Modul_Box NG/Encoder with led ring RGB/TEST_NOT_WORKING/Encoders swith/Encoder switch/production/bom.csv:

Designator,Footprint,Quantity,Value,LCSC Part #
C140,CP_Radial_D6.3mm_P2.50mm,1,100UF,
"C141, C142, C143",0603,3,100nf,
"H13, H14, H15, H16, H17, H18, H19, H20",MountingHole_3.2mm_M3,8,MountingHole,
"IC1, IC2, IC3",SOIC-16_3.9x9.9mm_P1.27mm,3,74HC165,
"J1, J2",IDC-Header_2x05_P2.54mm_Vertical,2,sin_in,
"J14, J15, J34, J35",PinHeader_1x03_P2.54mm_Vertical,4,Conn_01x06_Pin,
"J20, J21, J22, J23",PinSocket_1x06_P2.54mm_Vertical,4,Conn_01x06_Socket,
"J24, J25",PinSocket_1x03_P2.54mm_Vertical,2,Conn_01x06_Socket,
"J30, J31, J32, J33",PinHeader_1x06_P2.54mm_Vertical,4,Conn_01x06_Pin,
"J44, J45",IDC-Header_2x05_P2.54mm_Vertical,2,IDC-Header_2x05_P2.54mm_Vertical,
"R1, R10, R11, R12, R13, R14, R15, R16, R17, R18, R19, R2, R20, R21, R22, R23, R24, R25, R26, R27, R3, R4, R5, R6, R7, R8, R9",0603,27,10k,C1035
"SW1, SW2, SW3, SW4, SW5, SW6, SW7, SW8",PEC164120FS0012,8,PEC16-4XXXF-SXXXX,
